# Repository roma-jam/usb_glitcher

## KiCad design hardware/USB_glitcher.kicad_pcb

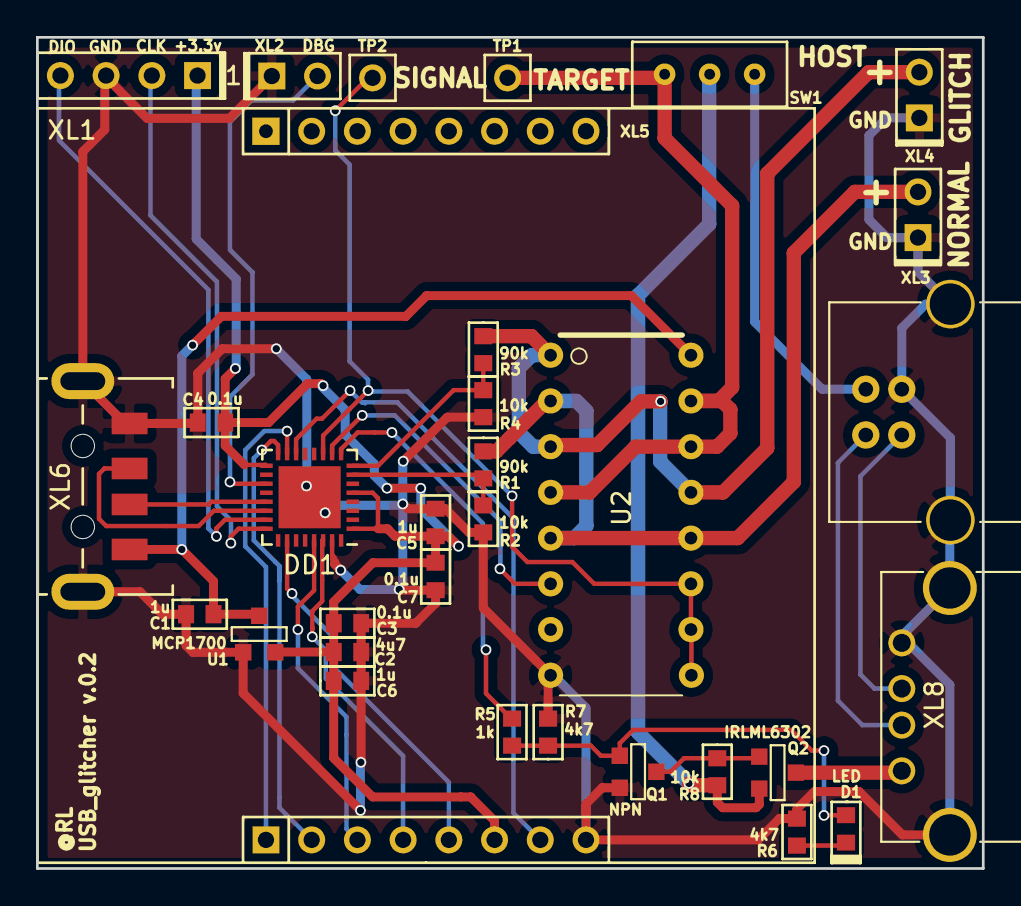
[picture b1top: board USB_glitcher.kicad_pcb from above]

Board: 2 copper layers, 52.6 x 46.2 mm, 32 parts (0 on the bottom side), 30 nets.

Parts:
C1, C5, C6: 1u; CAP_0603
C2: 4u7; CAP_0603
C3, C4, C7: 0.1u; CAP_0603
D1: LED; LED_0603
DD1: STM32F050K4_6; QFN-32-1EP_5x5mm_Pitch0.5mm
Q1: NPN; SOT23-3
Q2: IRLML6302; SOT23-3
R1, R3: 90k; RES_0603
R2, R4, R8: 10k; RES_0603
R5: 1k; RES_0603
R6, R7: 4k7; RES_0603
SW1: SWITCH; SW_SS-1P2T
TP1, TP2: TESTPOINT; PLS-1Rnd
U1: MCP1700; SOT23-3
U2: MAX4619
XL1: CONN_8; 84x48_LCD_Module
XL2, XL3, XL4: CONN_2; PLS-2
XL5: ST_SWD; PLS-4
XL6: USB_A; USB_A_Type2_PCB
XL7: USB_A; USB_B
XL8: USB_B; USB_A

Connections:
+3.3V: C2.1, C3.1, C4.1, C5.1, C6.1, C7.1, DD1.1, DD1.5, DD1.17, U1.2, XL1.6, XL5.1
+5V: C1.1, U1.3, U2.16, XL6.1
/DBG_TX: DD1.19, XL2.2
/DEVICE_POWER: Q2.2, R8.2, SW1.2
/DEVICE_POWER_EN: DD1.9, R5.2
/DM: XL7.2, XL8.2
/DP: XL7.3, XL8.3
/HOST_POWER: SW1.3, XL7.1
/LCD_BCKLT: DD1.14, XL1.7
/LCD_CE: DD1.16, XL1.2
/LCD_CLK: DD1.26, XL1.5
/LCD_DC: DD1.29, XL1.3
/LCD_DIN: DD1.30, XL1.4
/LCD_RESET: DD1.15, XL1.1
/LED: D1.A, Q1.1, R5.1, R7.1
/PWR: Q2.3, XL8.1
/SWCLK: DD1.24, XL5.2
/SWDIO: DD1.23, XL5.4
/TARGET_ENABLE: DD1.10, U2.6
/TARGET_SWITCH: DD1.11, TP2.1, U2.9, U2.10, U2.11
/USB_DM: DD1.21, XL6.2
/USB_DP: DD1.22, XL6.3
/Vglitch: R3.1, U2.1, U2.3, U2.13, XL4.2
/Vglitch_adc: DD1.8, R3.2, R4.1
/Vnorm_adc: DD1.7, R1.2, R2.1
/Vnormal: R1.1, U2.2, U2.5, U2.12, XL3.2
/Vtarget: SW1.1, TP1.1, U2.4, U2.14, U2.15
GND: C1.2, C2.2, C3.2, C4.2, C5.2, C6.2, C7.2, DD1.31, DD1.33, Q1.2, R2.2, R4.2, R6.1, R7.2, U1.1, U2.8, XL1.8, XL2.1, XL3.1, XL4.1, XL5.3, XL6.4, XL6.5, XL7.4, XL7.5, XL8.4, XL8.5
unnamed: D1.C, R6.2
unnamed: Q1.3, Q2.1, R8.1

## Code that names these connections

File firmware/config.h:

/*
    RExOS - embedded RTOS
    Copyright (c) 2011-2016, Alexey Kramarenko
    All rights reserved.
*/

#ifndef CONFIG_H
#define CONFIG_H

// TEST
#define DEVICE_TEST_TOGGLE_TIMEOUT_MS               5000

// =============================== PINs =======================================
#define DEVICE_POWER_PIN                            A3

#define DEVICE_MIN_DM_DP_DELAY_MS                   10
#define DEVICE_MIN_PERIOD_DELAY_MS                  1000

#define DEVICE_DEAFULT_DELAY_MS                     200
#define DEVICE_TEST_TIMEOUT_MS                      300

#define MULTIPLEXOR_TARGET_ENABLE_PIN               A4
#define MULTIPLEXOR_TARGET_SWITCH_PIN               A5

#define ADC_VOLTAGE_NORMAL_PIN                      A1
#define ADC_VOLTAGE_GLITCH_PIN                      A2

// ============================= ADC ===========================================
#define ADC_MEASURE_TIMEOUT_MS                      1000
#define ADC_REFERENCE_mV                            3300
#define ADC_RESOLUTION_BIT                          12
#define ADC_SAMPLE_RATE_160_5_CLK                   3

#define ADC_RESISTOR_DIVIDER                        (3.2)

// =============================== LEDS ========================================
#define LED_COUNT                                   4
#define LED_RED_PIN                                 A1
#define LED_BLUE_PIN                                A2
#define LED_ORANGE_PIN                              A15

#define LED_MAX_BRIGHT                              0xFF
#define LED_BLINK_FREQ_HZ                           25
#define LED_BLINK_TIMES                             3

#define LED_TIM_REG                                 TIM2
#define LED_TIM                                     TIM_2
#define LED_RED_CHANNEL                             TIM_CHANNEL2
#define LED_BLUE_CHANNEL                            TIM_CHANNEL3
#define LED_ORANGE_CHANNEL                          TIM_CHANNEL4

#define LED_BLINK_TIM_REG                           TIM3
#define LED_BLINK_TIM                               TIM_3
#define LED_BLINK_TIM_CHANNEL                       TIM_CHANNEL1
#define LED_BLINK_IRQ_VECTOR                        TIM3_IRQn

// ================================ LCD ========================================
#define LCD_TITLE_ROW                               0
#define LCD_ADC_NORMAL_MEAS_ROW                     1
#define LCD_ADC_GLITCH_MEAS_ROW                     2
#define LCD_ADC_VALUE_COLUMN                        7
#define LCD_ADC_MEAS_SCALE_COLUMN                   12

#define LCD_DEVICE_SWITCH_MODE_ROW                  4
#define LCD_DEVICE_SWITCH_MODE_COLUMN               5
#define LCD_DEVICE_STATE_ROW                        5


//#define LCD_FONT_WIDTH                              4
#define LCD_FONT_WIDTH                              5

#define LCD_DOT_FULL                                0x07
#define LCD_DOT_EMPTY                               0x09
#define LCD_BITBYTE                                 1
#define LCD_SPI                                     0

#define LCD_UPDATE_MS                               250
#define LCD_WIDTH                                   84
#define LCD_HEIGHT                                  48

#define LCD_STR_HEIGHT                              8
#define LCD_STR_WIDTH                               16

/* PINS */
#define LCD_BCKLT_PIN                               B0
#define LCD_RESET_PIN                               B1
#define LCD_CE_PIN                                  B2
#define LCD_SCLK_PIN                                B3
#define LCD_DC_PIN                                  B6
#define LCD_DIN_PIN                                 B7

// =============================== USB =========================================
#define USB_PORT_NUM                                USB_0
#define USBD_PROCESS_SIZE                           1200
#define USBD_PROCESS_PRIORITY                       150

// ============================== CCID  ========================================
#define USB_CCID_INTERFACE                          0
#define USB_HID_INTERFACE                           0

// =============================== COMM ========================================
#define COMM_COMMAND_END                            0x0D

// ================================= DEBUG =====================================

#define DBG_CONSOLE                                 UART_1
#define DBG_CONSOLE_TX_PIN                          A9
#define DBG_CONSOLE_BAUD                            115200

#define TEST_ROUNDS                                 10000

#define APP_DEBUG                                   1
#define APP_DEBUG_ERRORS                            1

#define APP_DEBUG_USB                               0
#define APP_DEBUG_HID                               0
#define APP_DEBUG_DEVICE                            0

#endif // CONFIG_H

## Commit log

2019-05-29 + Add pcb
2020-02-20 PCB v.0.2 + Fix Vcc MAX4619. + Fix layout for testpoint. + Fix SWDIO and USB pin mapping. + Fix resistor divider before NPN transistor.
2020-02-20 Add firmware project.
